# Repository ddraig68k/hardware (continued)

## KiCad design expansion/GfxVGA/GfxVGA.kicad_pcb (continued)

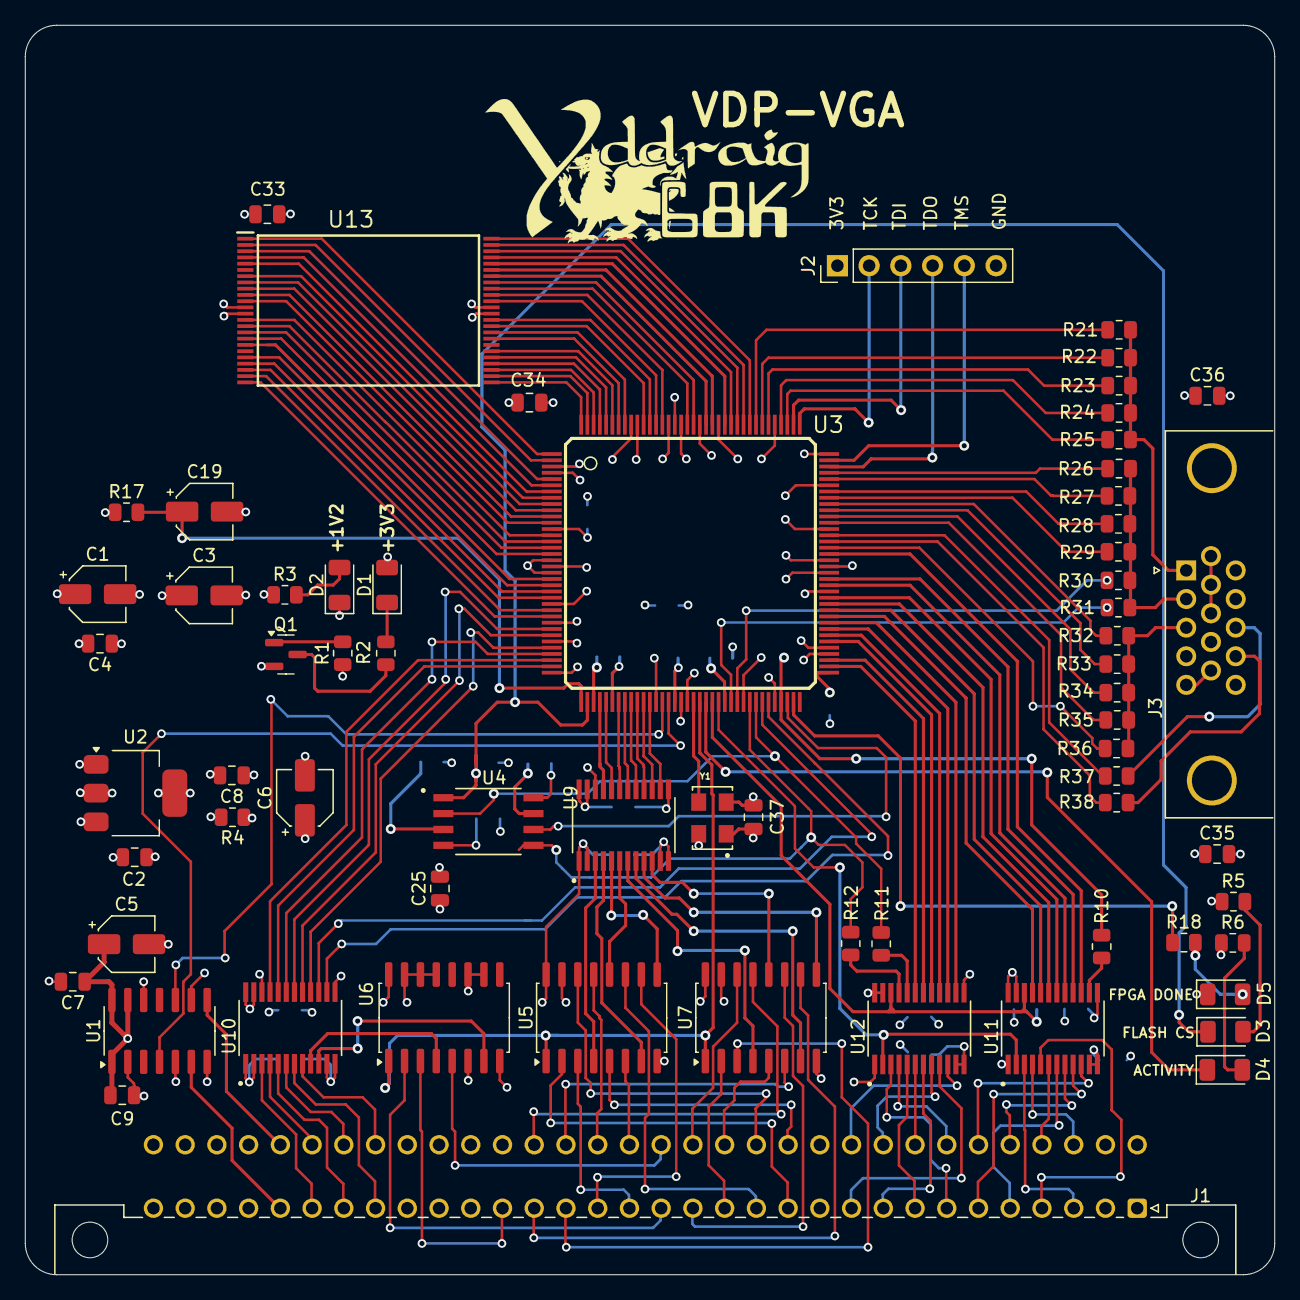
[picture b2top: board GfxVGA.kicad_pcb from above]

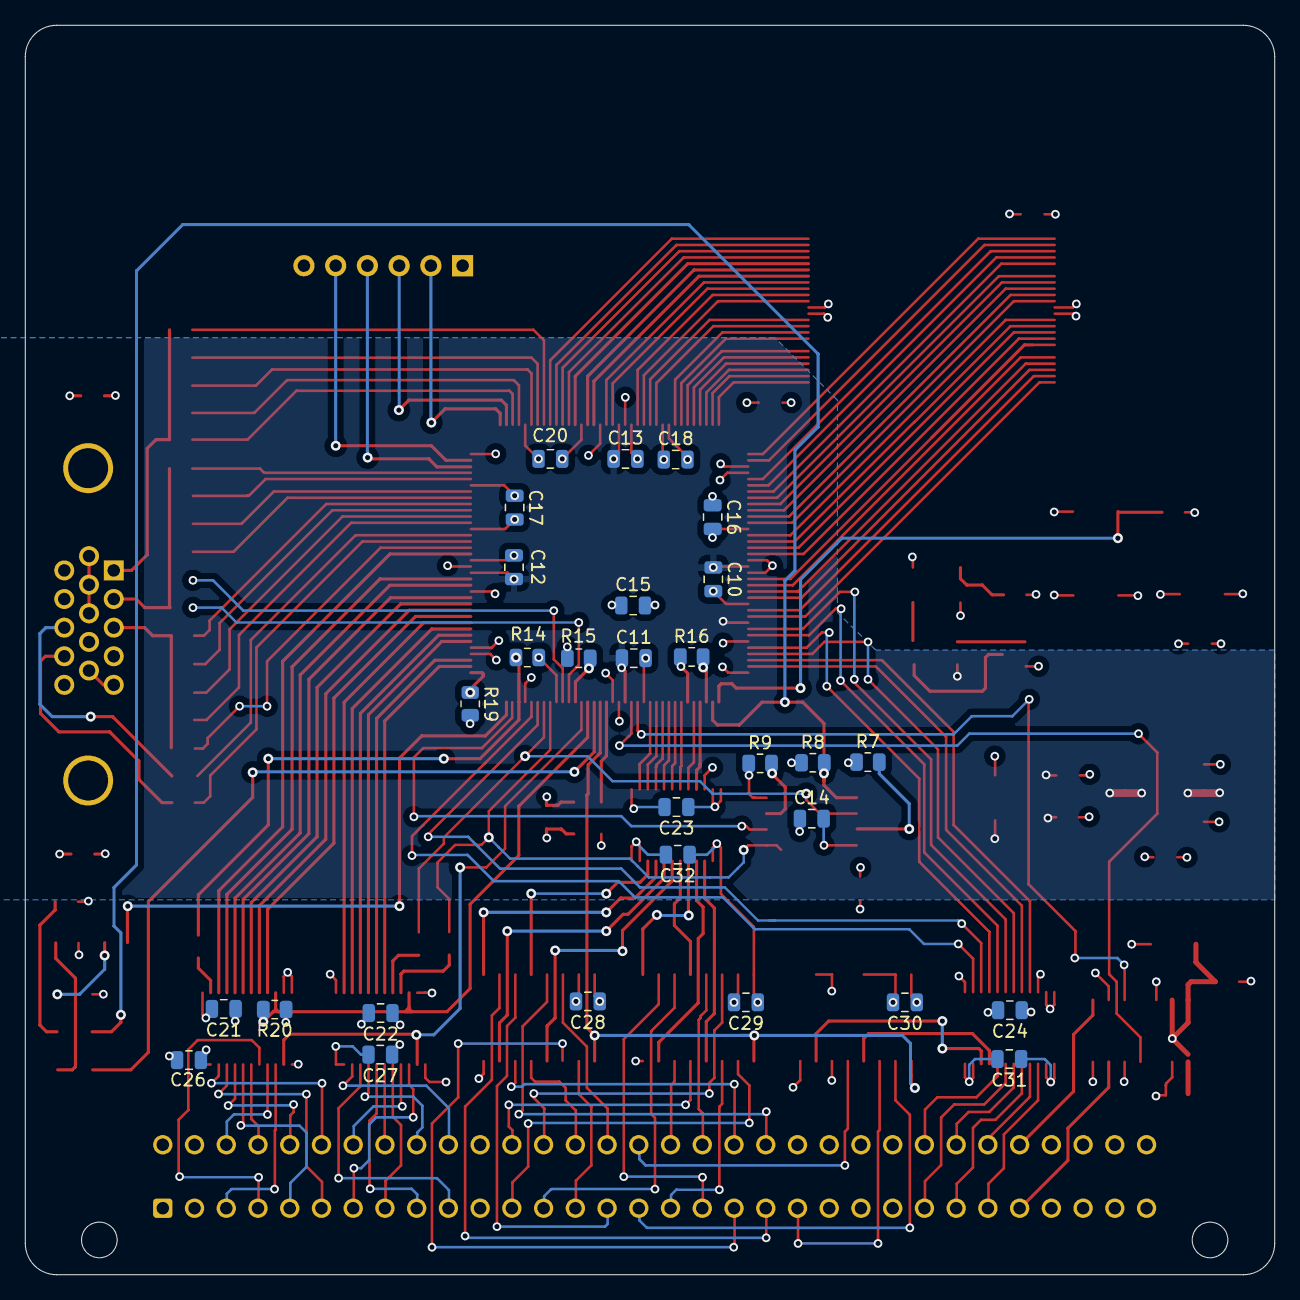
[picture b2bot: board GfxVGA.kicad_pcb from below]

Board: 4 copper layers, 100.0 x 100.0 mm, 97 parts (29 on the bottom side), 183 nets.

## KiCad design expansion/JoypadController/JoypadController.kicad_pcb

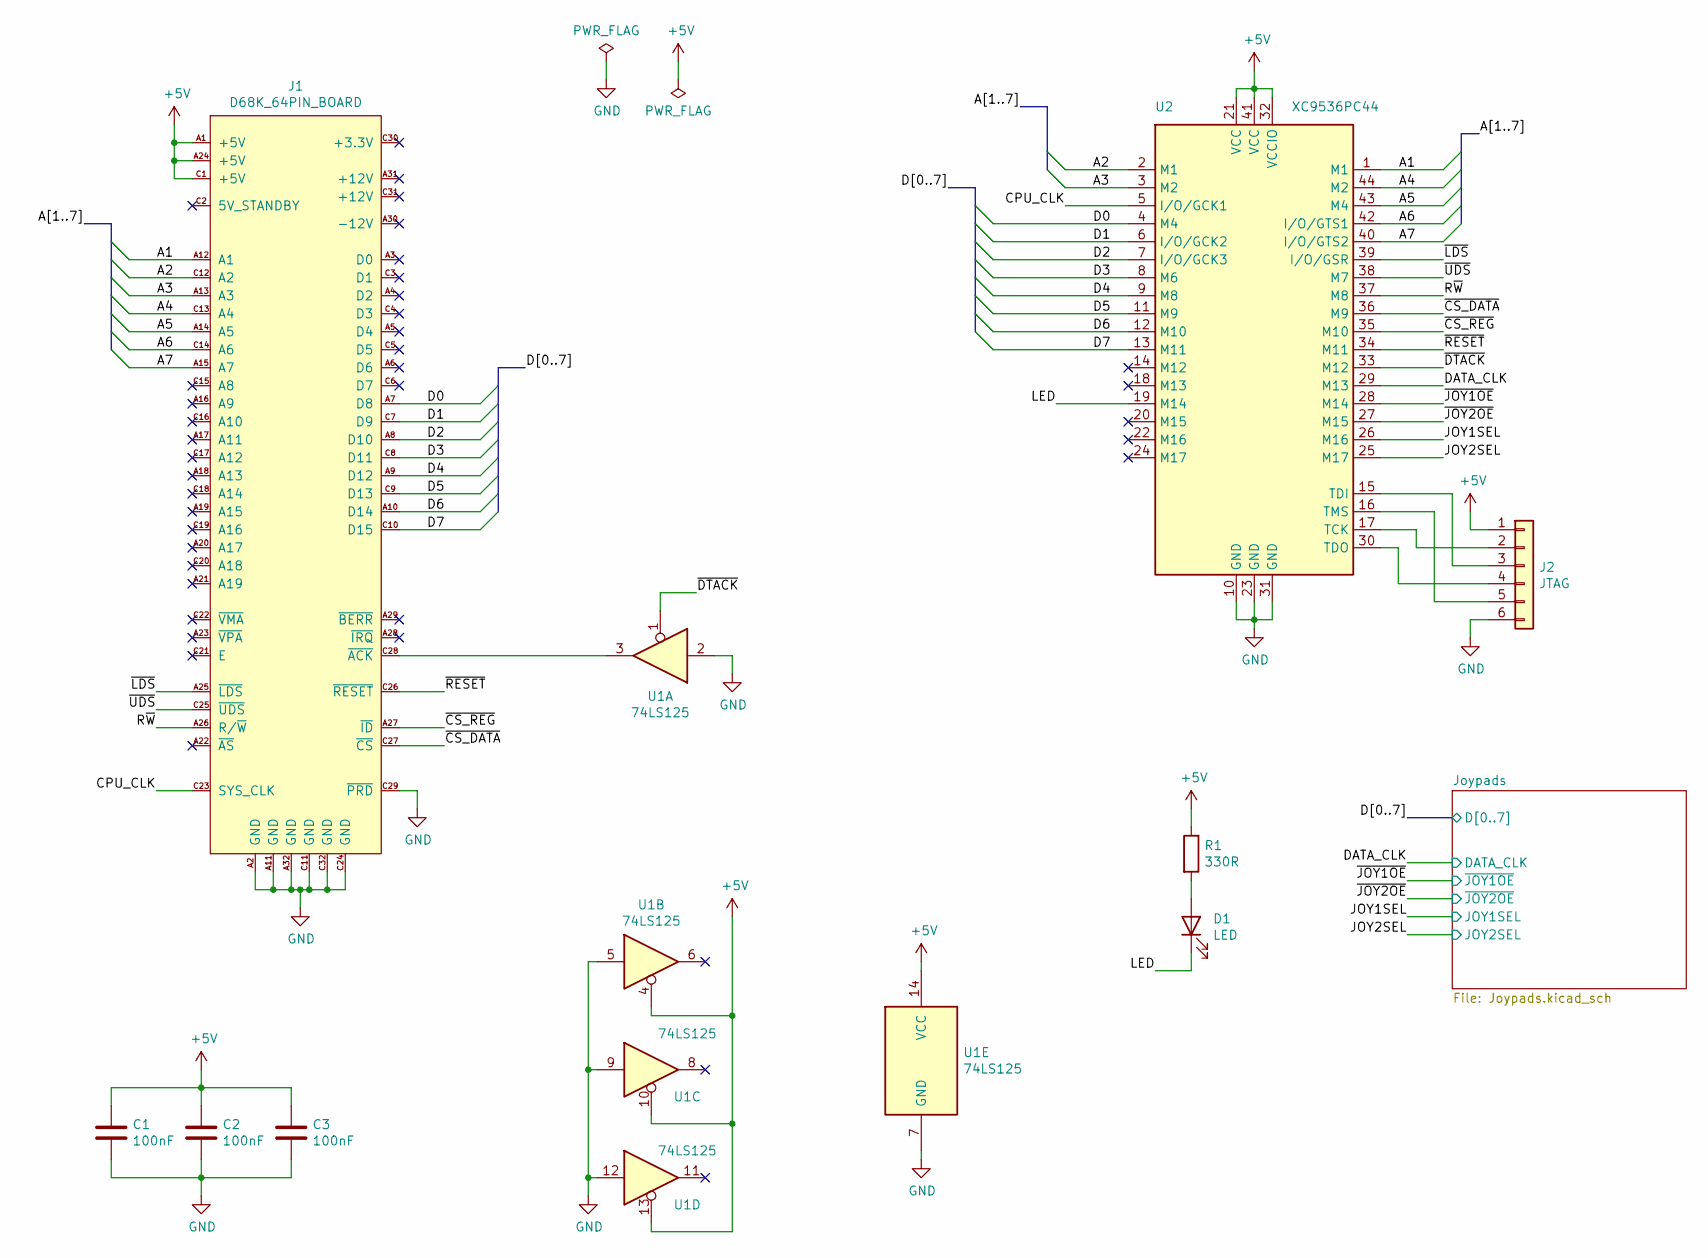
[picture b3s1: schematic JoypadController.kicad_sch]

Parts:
C1, C2, C3: 100nF; C_Disc_D5.0mm_W2.5mm_P2.50mm
D1: LED; LED_D5.0mm
J1: D68K_64PIN_BOARD; DIN41612_C_2x32_Male_Horizontal_THT
J2: JTAG; PinHeader_1x06_P2.54mm_Vertical
R1: 330R; R_Axial_DIN0207_L6.3mm_D2.5mm_P10.16mm_Horizontal
U1: 74LS125; DIP-14_W7.62mm_Socket
U2: XC9536PC44; PLCC-44

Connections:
+5V: C1.1, C2.1, C3.1, J1.A1 (+5V), J1.A24 (+5V), J1.C1 (+5V), J2.1, R1.1, U1.4, U1.10, U1.13, U1.14 (VCC), U2.21 (VCC), U2.32 (VCCIO), U2.41 (VCC); also elsewhere on the board
/A1: J1.A12 (A1), U2.1 (M1)
/A2: J1.C12 (A2), U2.2 (M1)
/A3: J1.A13 (A3), U2.3 (M2)
/A4: J1.C13 (A4), U2.44 (M2)
/A5: J1.A14 (A5), U2.43 (M4)
/A6: J1.C14 (A6), U2.42 (I/O/GTS1)
/A7: J1.A15 (A7), U2.40 (I/O/GTS2)
/CPU_CLK: J1.C23 (SYS_CLK), U2.5 (I/O/GCK1)
/D0: J1.A7 (D8), U2.4 (M4); also elsewhere on the board
/D1: J1.C7 (D9), U2.6 (I/O/GCK2); also elsewhere on the board
/D2: J1.A8 (D10), U2.7 (I/O/GCK3); also elsewhere on the board
/D3: J1.C8 (D11), U2.8 (M6); also elsewhere on the board
/D4: J1.A9 (D12), U2.9 (M8); also elsewhere on the board
/D5: J1.C9 (D13), U2.11 (M9); also elsewhere on the board
/D6: J1.A10 (D14), U2.12 (M10); also elsewhere on the board
/D7: J1.C10 (D15), U2.13 (M11); also elsewhere on the board
/DATA_CLK: U2.29 (M13); also elsewhere on the board
/JOY1SEL: U2.26 (M16); also elsewhere on the board
/JOY2SEL: U2.25 (M17); also elsewhere on the board
/LED: D1.1 (K), U2.19 (M14)
/R~W: J1.A26 (R/~W), U2.37 (M8)
/~CS_DATA: J1.C27 (~CS), U2.36 (M9)
/~CS_REG: J1.A27 (~ID), U2.35 (M10)
/~DTACK: U1.1, U2.33 (M12)
/~JOY1OE: U2.28 (M14); also elsewhere on the board
/~JOY2OE: U2.27 (M15); also elsewhere on the board
/~LDS: J1.A25 (~LDS), U2.39 (I/O/GSR)
/~RESET: J1.C26 (~RESET), U2.34 (M11)
/~UDS: J1.C25 (~UDS), U2.38 (M7)
GND: C1.2, C2.2, C3.2, J1.A2 (GND), J1.A11 (GND), J1.A32 (GND), J1.C11 (GND), J1.C24 (GND), J1.C29 (~PRD), J1.C32 (GND), J2.6, U1.2, U1.5, U1.7 (GND), U1.9, U1.12, U2.10 (GND), U2.23 (GND), U2.31 (GND); also elsewhere on the board
unnamed: D1.2 (A), R1.2
unnamed: J1.C28 (~ACK), U1.3
unnamed: J2.2, U2.17 (TCK)
unnamed: J2.3, U2.15 (TDI)
unnamed: J2.4, U2.30 (TDO)
unnamed: J2.5, U2.16 (TMS)

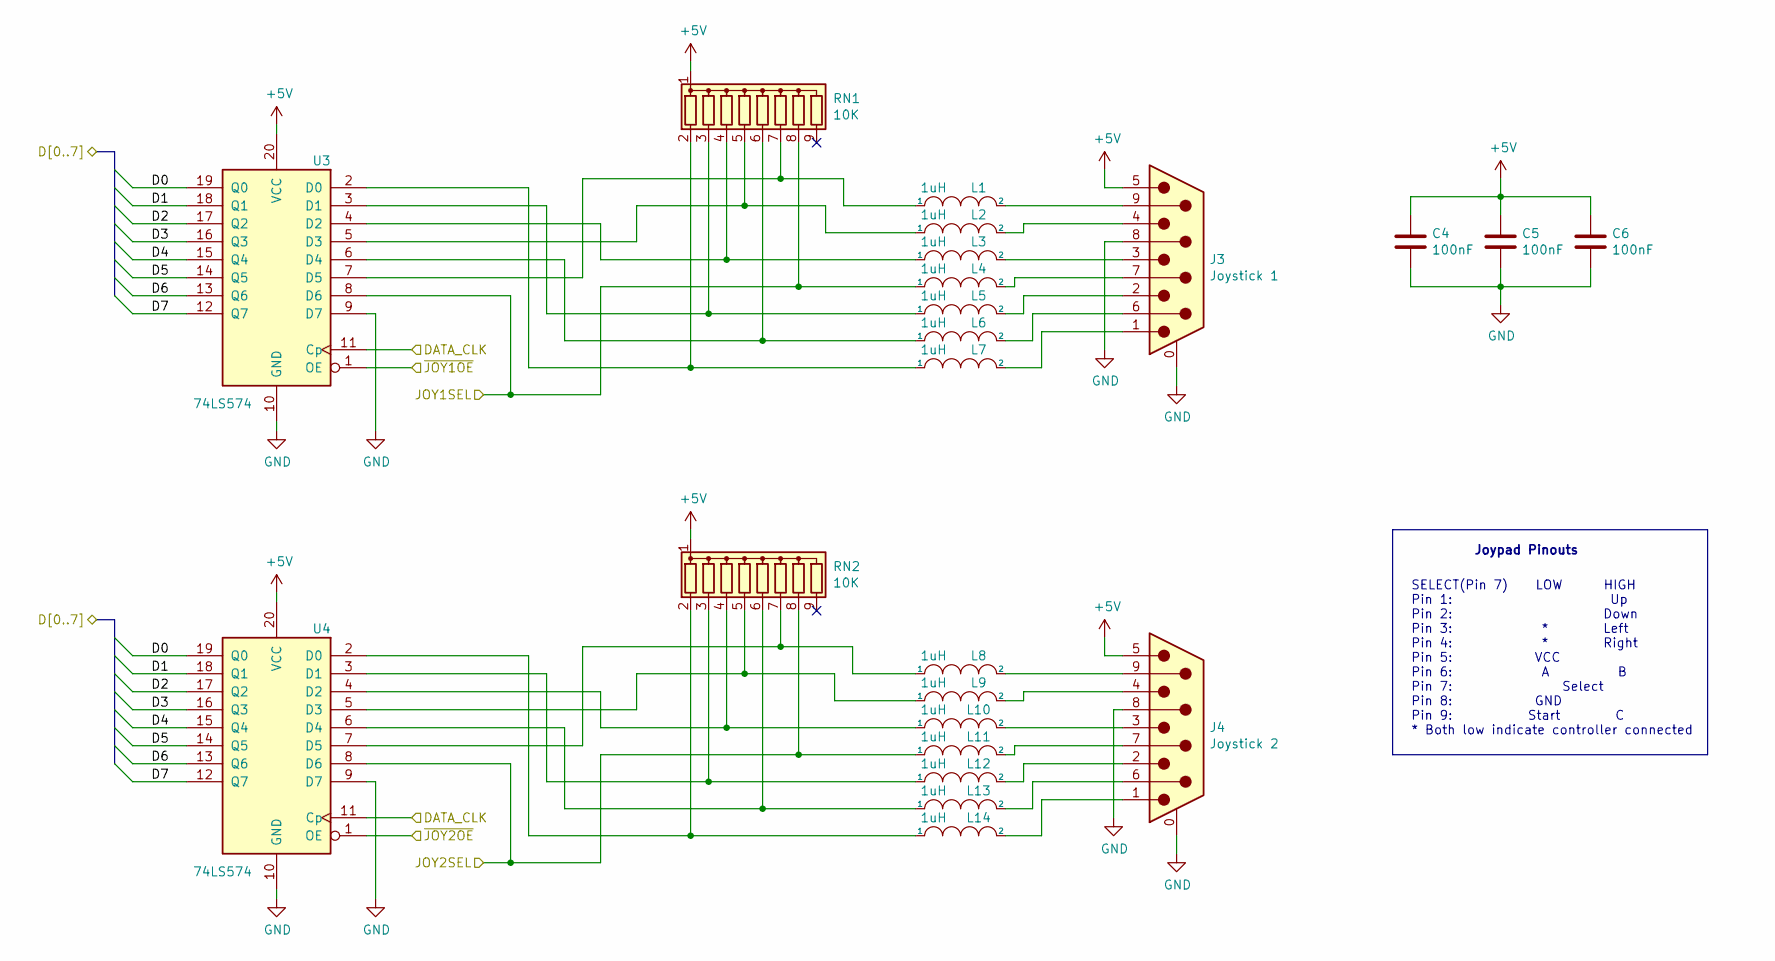
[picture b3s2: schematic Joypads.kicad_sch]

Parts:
C4, C5, C6: 100nF; C_Disc_D5.0mm_W2.5mm_P2.50mm
J3: Joystick 1; DSUB-9_Male_Horizontal_P2.77x2.84mm_EdgePinOffset4.94mm_Hou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
J4: Joystick 2; DSUB-9_Male_Horizontal_P2.77x2.84mm_EdgePinOffset4.94mm_Hou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
L1, L2, L3, L4, L5, L6, L7, L8, L9, L10, L11, L12, L13, L14: 1uH; L_Axial_L6.6mm_D2.7mm_P10.16mm_Horizontal_Vishay_IM-2
RN1, RN2: 10K; R_Array_SIP9
U3, U4: 74LS574; DIP-20_W7.62mm_Socket

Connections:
+5V: C4.1, C5.1, C6.1, J3.5, J4.5, RN1.1 (common), RN2.1 (common), U3.20 (VCC), U4.20 (VCC); also elsewhere on the board
/D0: U3.19 (Q0), U4.19 (Q0); also elsewhere on the board
/D1: U3.18 (Q1), U4.18 (Q1); also elsewhere on the board
/D2: U3.17 (Q2), U4.17 (Q2); also elsewhere on the board
/D3: U3.16 (Q3), U4.16 (Q3); also elsewhere on the board
/D4: U3.15 (Q4), U4.15 (Q4); also elsewhere on the board
/D5: U3.14 (Q5), U4.14 (Q5); also elsewhere on the board
/D6: U3.13 (Q6), U4.13 (Q6); also elsewhere on the board
/D7: U3.12 (Q7), U4.12 (Q7); also elsewhere on the board
/DATA_CLK: U3.11 (Cp), U4.11 (Cp); also elsewhere on the board
/JOY1SEL: L4.1, RN1.8 (R7), U3.8 (D6); also elsewhere on the board
/JOY2SEL: L11.1, RN2.8 (R7), U4.8 (D6); also elsewhere on the board
/~JOY1OE: U3.1 (OE); also elsewhere on the board
/~JOY2OE: U4.1 (OE); also elsewhere on the board
GND: C4.2, C5.2, C6.2, J3.0 (PAD), J3.8, J4.0 (PAD), J4.8, U3.9 (D7), U3.10 (GND), U4.9 (D7), U4.10 (GND); also elsewhere on the board
unnamed: J3.1, L7.2
unnamed: J3.2, L5.2
unnamed: J3.3, L3.2
unnamed: J3.4, L2.2
unnamed: J3.6, L6.2
unnamed: J3.7, L4.2
unnamed: J3.9, L1.2
unnamed: J4.1, L14.2
unnamed: J4.2, L12.2
unnamed: J4.3, L10.2
unnamed: J4.4, L9.2
unnamed: J4.6, L13.2
unnamed: J4.7, L11.2
unnamed: J4.9, L8.2
unnamed: L1.1, RN1.7 (R6), U3.7 (D5)
unnamed: L2.1, RN1.5 (R4), U3.5 (D3)
unnamed: L3.1, RN1.4 (R3), U3.4 (D2)
unnamed: L5.1, RN1.3 (R2), U3.3 (D1)
unnamed: L6.1, RN1.6 (R5), U3.6 (D4)
unnamed: L7.1, RN1.2 (R1), U3.2 (D0)
unnamed: L8.1, RN2.7 (R6), U4.7 (D5)
unnamed: L9.1, RN2.5 (R4), U4.5 (D3)
unnamed: L10.1, RN2.4 (R3), U4.4 (D2)
unnamed: L12.1, RN2.3 (R2), U4.3 (D1)
unnamed: L13.1, RN2.6 (R5), U4.6 (D4)
unnamed: L14.1, RN2.2 (R1), U4.2 (D0)

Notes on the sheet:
SELECT(Pin 7) LOW HIGH Pin 1: Up Pin 2: Down Pin 3: * Left Pin 4: * Right Pin 5: VCC Pin 6: A B Pin 7: Select Pin 8: GND Pin 9: Start C * Both low indicate controller connected
Joypad Pinouts

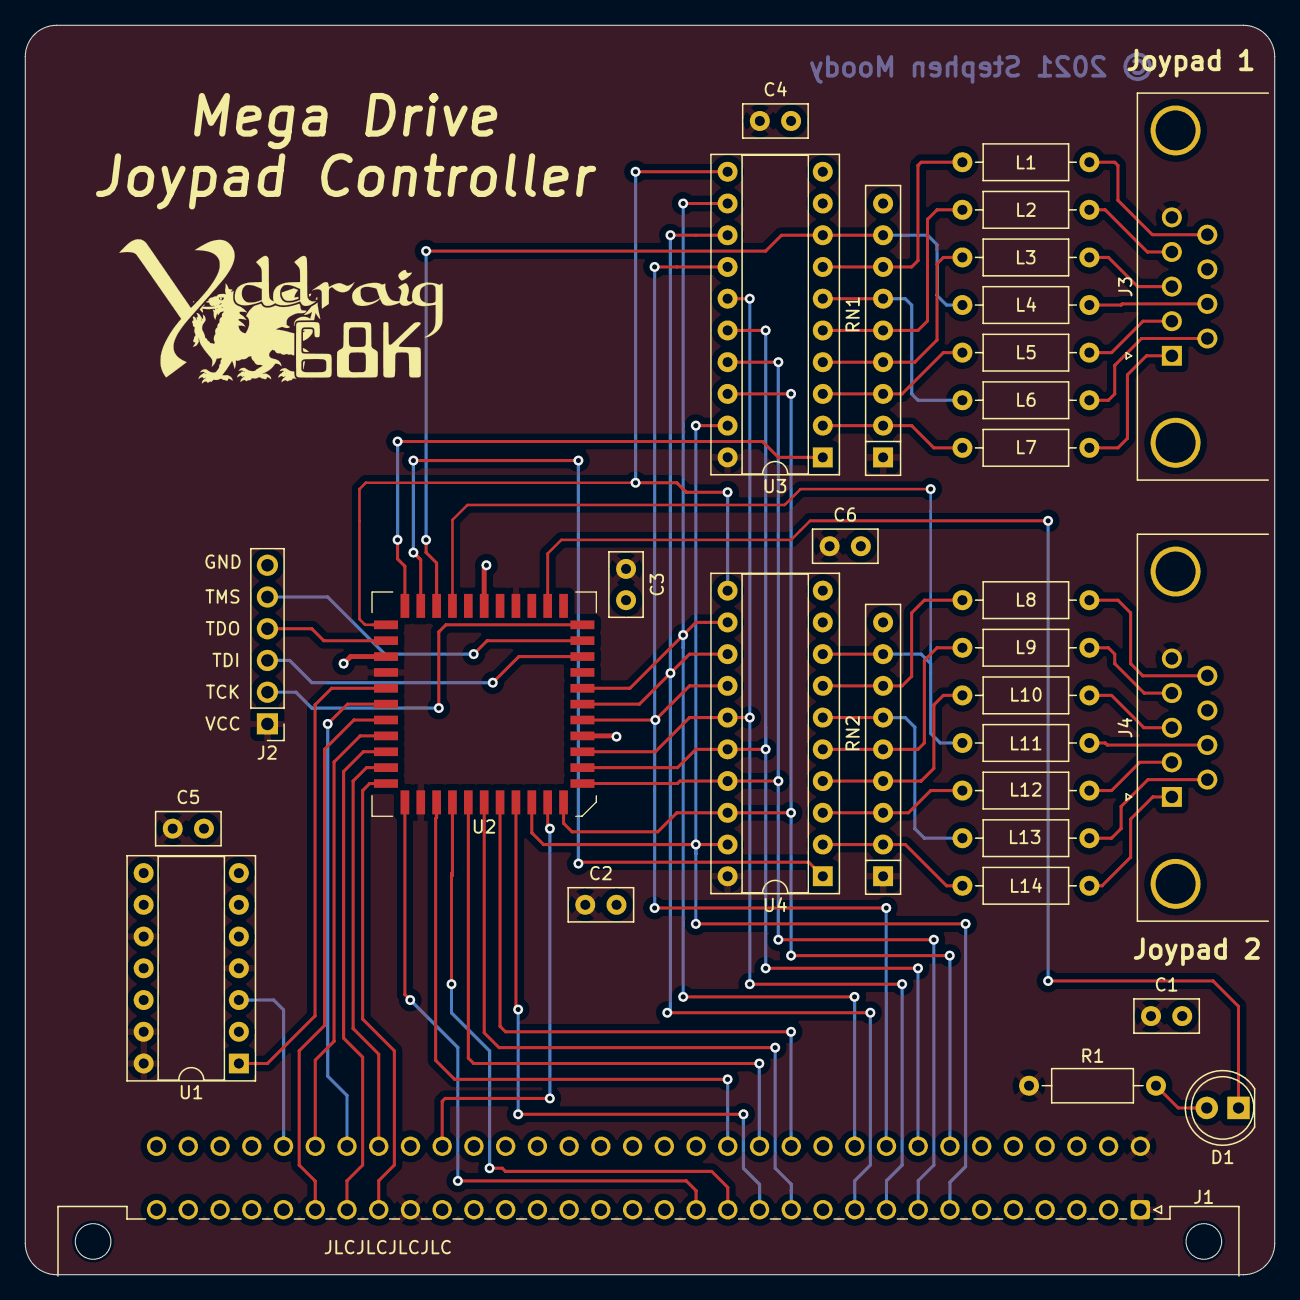
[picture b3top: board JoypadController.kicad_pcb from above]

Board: 2 copper layers, 100.0 x 100.0 mm, 32 parts (0 on the bottom side), 63 nets.

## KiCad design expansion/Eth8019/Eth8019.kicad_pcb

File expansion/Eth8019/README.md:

# RTL8019 Ethernet Card

The Realtek RTL8019AS is a fully integrated, single-chip [NE2000](https://en.wikipedia.org/wiki/NE2000)-compatible Ethernet controller with an 8/16-bit ISA-style bus interface and an integrated packet buffer, which makes it straightforward to attach to a simple non-DMA host bus like the 68000's.

A Xilinx XC9536PC44 CPLD provides the address decoding and glue logic between the expansion bus and the RTL8019AS, including the IOCS16B signalling used to negotiate 8/16-bit bus width with the host, as on ISA NE2000 cards.

The card has an RJ45 jack with integrated magnetics for the 10BASE-T connection, link/activity LEDs, and a JTAG header for programming the CPLD.

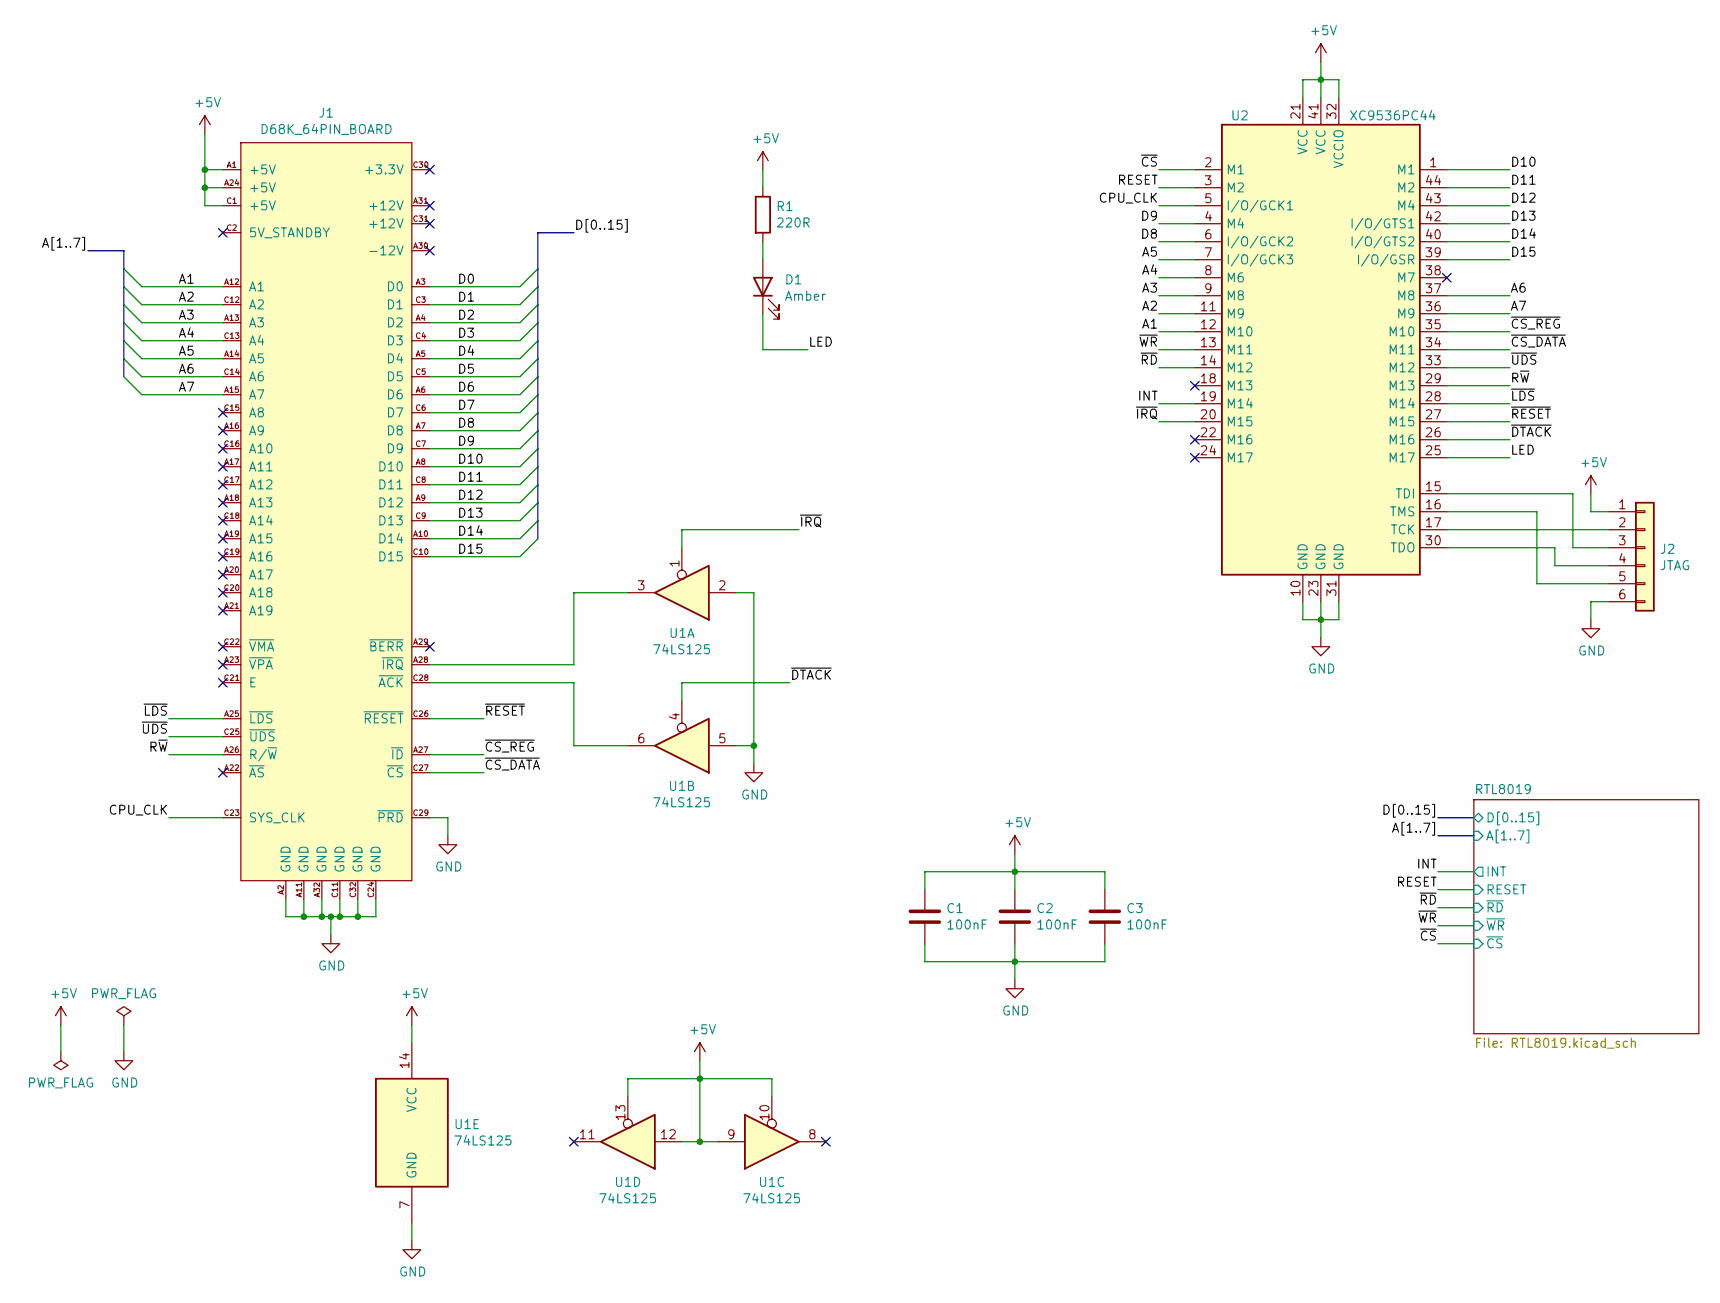
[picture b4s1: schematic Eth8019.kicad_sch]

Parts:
C1, C2, C3: 100nF; C_0805_2012Metric
D1: Amber; LED_1206_3216Metric
J1: D68K_64PIN_BOARD; DIN41612_C_2x32_Male_Horizontal_THT
J2: JTAG; PinHeader_1x06_P2.54mm_Vertical
R1: 220R; R_0805_2012Metric
U1: 74LS125; SO-14_5.3x10.2mm_P1.27mm
U2: XC9536PC44; PLCC-44

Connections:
+5V: C1.1, C2.1, C3.1, J1.A1 (+5V), J1.A24 (+5V), J1.C1 (+5V), J2.1, R1.1, U1.9, U1.10, U1.12, U1.13, U1.14 (VCC), U2.21 (VCC), U2.32 (VCCIO), U2.41 (VCC); also elsewhere on the board
/A1: J1.A12 (A1), U2.12 (M10); also elsewhere on the board
/A2: J1.C12 (A2), U2.11 (M9); also elsewhere on the board
/A3: J1.A13 (A3), U2.9 (M8); also elsewhere on the board
/A4: J1.C13 (A4), U2.8 (M6); also elsewhere on the board
/A5: J1.A14 (A5), U2.7 (I/O/GCK3); also elsewhere on the board
/A6: J1.C14 (A6), U2.37 (M8)
/A7: J1.A15 (A7), U2.36 (M9)
/CPU_CLK: J1.C23 (SYS_CLK), U2.5 (I/O/GCK1)
/D0: J1.A3 (D0); also elsewhere on the board
/D1: J1.C3 (D1); also elsewhere on the board
/D2: J1.A4 (D2); also elsewhere on the board
/D3: J1.C4 (D3); also elsewhere on the board
/D4: J1.A5 (D4); also elsewhere on the board
/D5: J1.C5 (D5); also elsewhere on the board
/D6: J1.A6 (D6); also elsewhere on the board
/D7: J1.C6 (D7); also elsewhere on the board
/D8: J1.A7 (D8), U2.6 (I/O/GCK2); also elsewhere on the board
/D9: J1.C7 (D9), U2.4 (M4); also elsewhere on the board
/D10: J1.A8 (D10), U2.1 (M1); also elsewhere on the board
/D11: J1.C8 (D11), U2.44 (M2); also elsewhere on the board
/D12: J1.A9 (D12), U2.43 (M4); also elsewhere on the board
/D13: J1.C9 (D13), U2.42 (I/O/GTS1); also elsewhere on the board
/D14: J1.A10 (D14), U2.40 (I/O/GTS2); also elsewhere on the board
/D15: J1.C10 (D15), U2.39 (I/O/GSR); also elsewhere on the board
/INT: U2.19 (M14); also elsewhere on the board
/LED: D1.1 (K), U2.25 (M17)
/RESET: U2.3 (M2); also elsewhere on the board
/R~W: J1.A26 (R/~W), U2.29 (M13)
/~CS_DATA: J1.C27 (~CS), U2.34 (M11)
/~CS_REG: J1.A27 (~ID), U2.35 (M10)
/~CS: U2.2 (M1); also elsewhere on the board
/~DTACK: U1.4, U2.26 (M16)
/~IRQ: U1.1, U2.20 (M15)
/~LDS: J1.A25 (~LDS), U2.28 (M14)
/~RD: U2.14 (M12); also elsewhere on the board
/~RESET: J1.C26 (~RESET), U2.27 (M15)
/~UDS: J1.C25 (~UDS), U2.33 (M12)
/~WR: U2.13 (M11); also elsewhere on the board
GND: C1.2, C2.2, C3.2, J1.A2 (GND), J1.A11 (GND), J1.A32 (GND), J1.C11 (GND), J1.C24 (GND), J1.C29 (~PRD), J1.C32 (GND), J2.6, U1.2, U1.5, U1.7 (GND), U2.10 (GND), U2.23 (GND), U2.31 (GND); also elsewhere on the board
unnamed: D1.2 (A), R1.2
unnamed: J1.A28 (~IRQ), U1.3
unnamed: J1.C28 (~ACK), U1.6
unnamed: J2.2, U2.17 (TCK)
unnamed: J2.3, U2.15 (TDI)
unnamed: J2.4, U2.30 (TDO)
unnamed: J2.5, U2.16 (TMS)

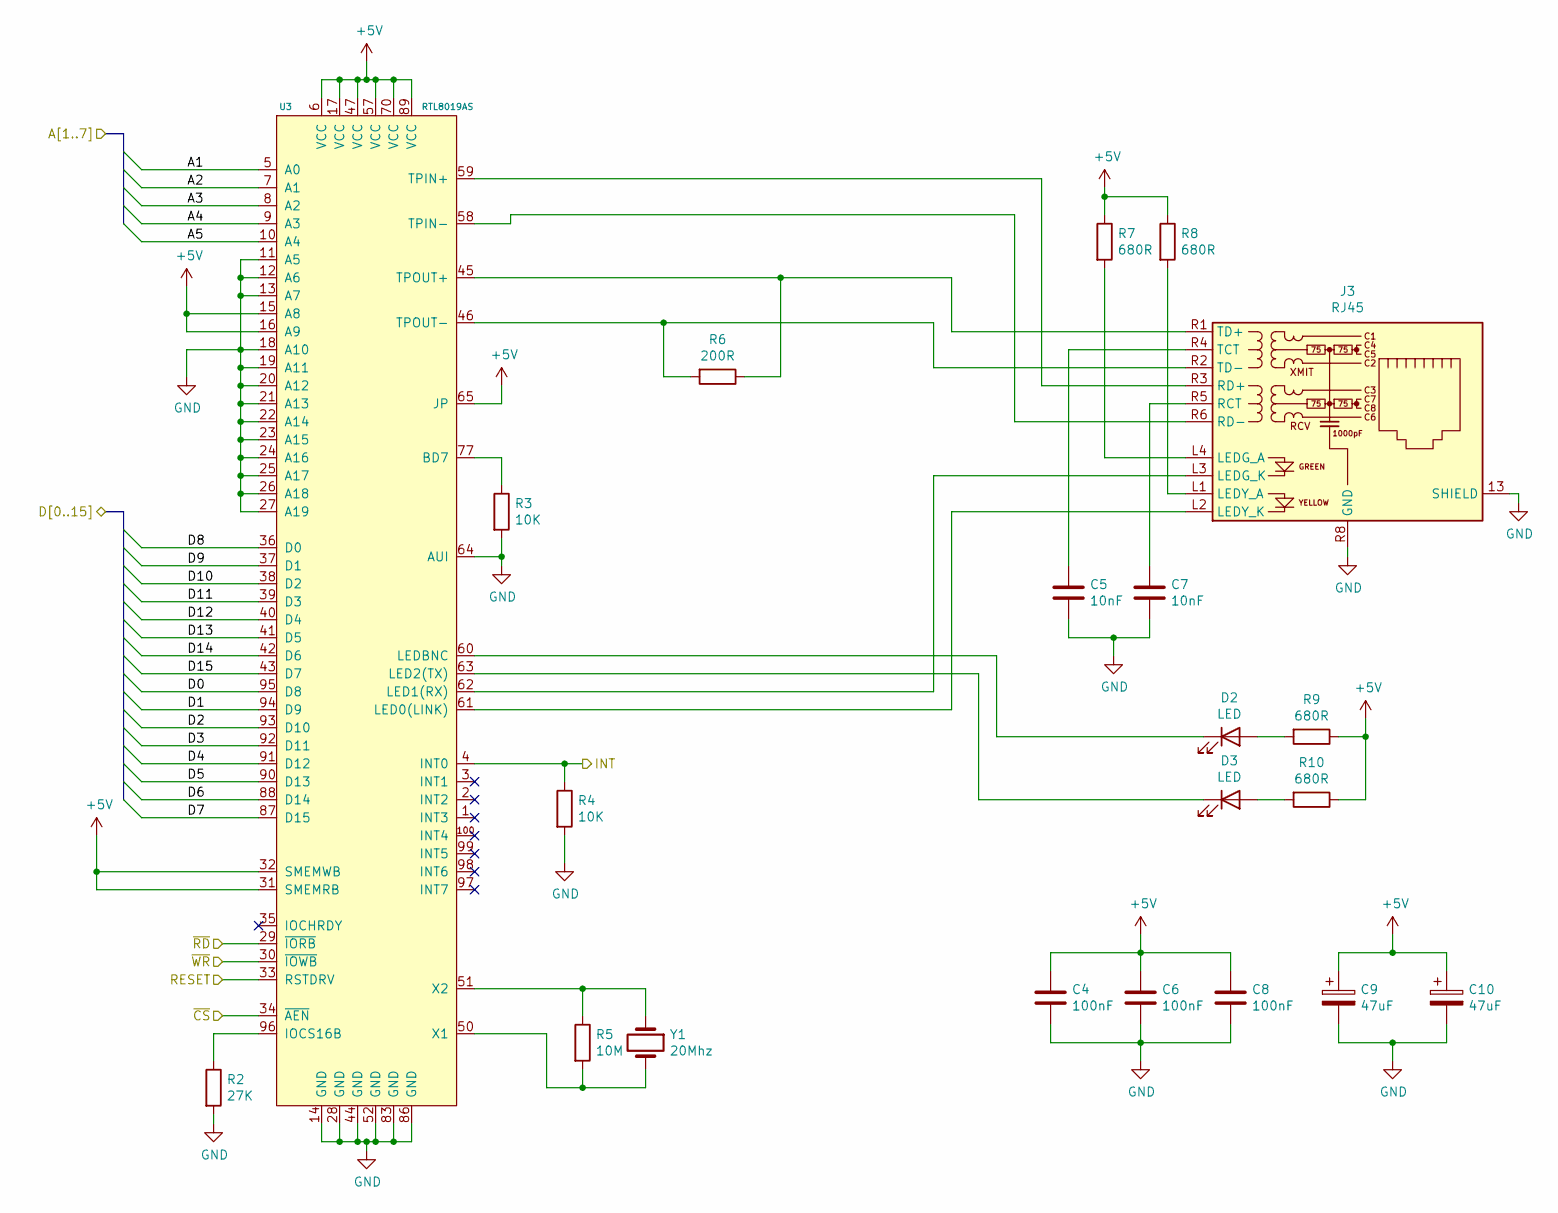
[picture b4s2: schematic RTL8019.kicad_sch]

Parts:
C4, C6, C8: 100nF; C_0805_2012Metric
C5, C7: 10nF; C_0805_2012Metric
C9, C10: 47uF; CP_Elec_4x5.7
D2, D3: LED; LED_1206_3216Metric
J3: RJ45; RJ45_Amphenol_RJMG1BD3B8K1ANR
R2: 27K; R_0805_2012Metric
R3, R4: 10K; R_0805_2012Metric
R5: 10M; R_0805_2012Metric
R6: 200R; R_0805_2012Metric
R7, R8, R9, R10: 680R; R_0805_2012Metric
U3: RTL8019AS
Y1: 20Mhz; Crystal_SMD_HC49-SD

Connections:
+5V: C4.1, C6.1, C8.1, C9.1, C10.1, R7.1, R8.1, R9.1, R10.1, U3.6 (VCC), U3.15 (A8), U3.16 (A9), U3.17 (VCC), U3.31 (SMEMRB), U3.32 (SMEMWB), U3.47 (VCC), U3.57 (VCC), U3.65 (JP), U3.70 (VCC), U3.89 (VCC); also elsewhere on the board
/A1: U3.5 (A0); also elsewhere on the board
/A2: U3.7 (A1); also elsewhere on the board
/A3: U3.8 (A2); also elsewhere on the board
/A4: U3.9 (A3); also elsewhere on the board
/A5: U3.10 (A4); also elsewhere on the board
/D0: U3.95 (D8); also elsewhere on the board
/D1: U3.94 (D9); also elsewhere on the board
/D2: U3.93 (D10); also elsewhere on the board
/D3: U3.92 (D11); also elsewhere on the board
/D4: U3.91 (D12); also elsewhere on the board
/D5: U3.90 (D13); also elsewhere on the board
/D6: U3.88 (D14); also elsewhere on the board
/D7: U3.87 (D15); also elsewhere on the board
/D8: U3.36 (D0); also elsewhere on the board
/D9: U3.37 (D1); also elsewhere on the board
/D10: U3.38 (D2); also elsewhere on the board
/D11: U3.39 (D3); also elsewhere on the board
/D12: U3.40 (D4); also elsewhere on the board
/D13: U3.41 (D5); also elsewhere on the board
/D14: U3.42 (D6); also elsewhere on the board
/D15: U3.43 (D7); also elsewhere on the board
/INT: R4.1, U3.4 (INT0); also elsewhere on the board
/RESET: U3.33 (RSTDRV); also elsewhere on the board
/~CS: U3.34 (~AEN); also elsewhere on the board
/~RD: U3.29 (~IORB); also elsewhere on the board
/~WR: U3.30 (~IOWB); also elsewhere on the board
GND: C4.2, C5.2, C6.2, C7.2, C8.2, C9.2, C10.2, J3.13 (SHIELD), J3.R8 (GND), R2.2, R3.2, R4.2, U3.11 (A5), U3.12 (A6), U3.13 (A7), U3.14 (GND), U3.18 (A10), U3.19 (A11), U3.20 (A12), U3.21 (A13), U3.22 (A14), U3.23 (A15), U3.24 (A16), U3.25 (A17), U3.26 (A18), U3.27 (A19), U3.28 (GND), U3.44 (GND), U3.52 (GND), U3.64 (AUI), U3.83 (GND), U3.86 (GND); also elsewhere on the board
unnamed: C5.1, J3.R4 (TCT)
unnamed: C7.1, J3.R5 (RCT)
unnamed: D2.1 (K), U3.60 (LEDBNC)
unnamed: D2.2 (A), R9.2
unnamed: D3.1 (K), U3.63 (LED2(TX))
unnamed: D3.2 (A), R10.2
unnamed: J3.L1 (LEDY_A), R8.2
unnamed: J3.L2 (LEDY_K), U3.61 (LED0(LINK))
unnamed: J3.L3 (LEDG_K), U3.62 (LED1(RX))
unnamed: J3.L4 (LEDG_A), R7.2
unnamed: J3.R1 (TD+), R6.1, U3.45 (TPOUT+)
unnamed: J3.R2 (TD-), R6.2, U3.46 (TPOUT-)
unnamed: J3.R3 (RD+), U3.59 (TPIN+)
unnamed: J3.R6 (RD-), U3.58 (TPIN-)
unnamed: R2.1, U3.96 (IOCS16B)
unnamed: R3.1, U3.77 (BD7)
unnamed: R5.1, U3.51 (X2), Y1.1
unnamed: R5.2, U3.50 (X1), Y1.2

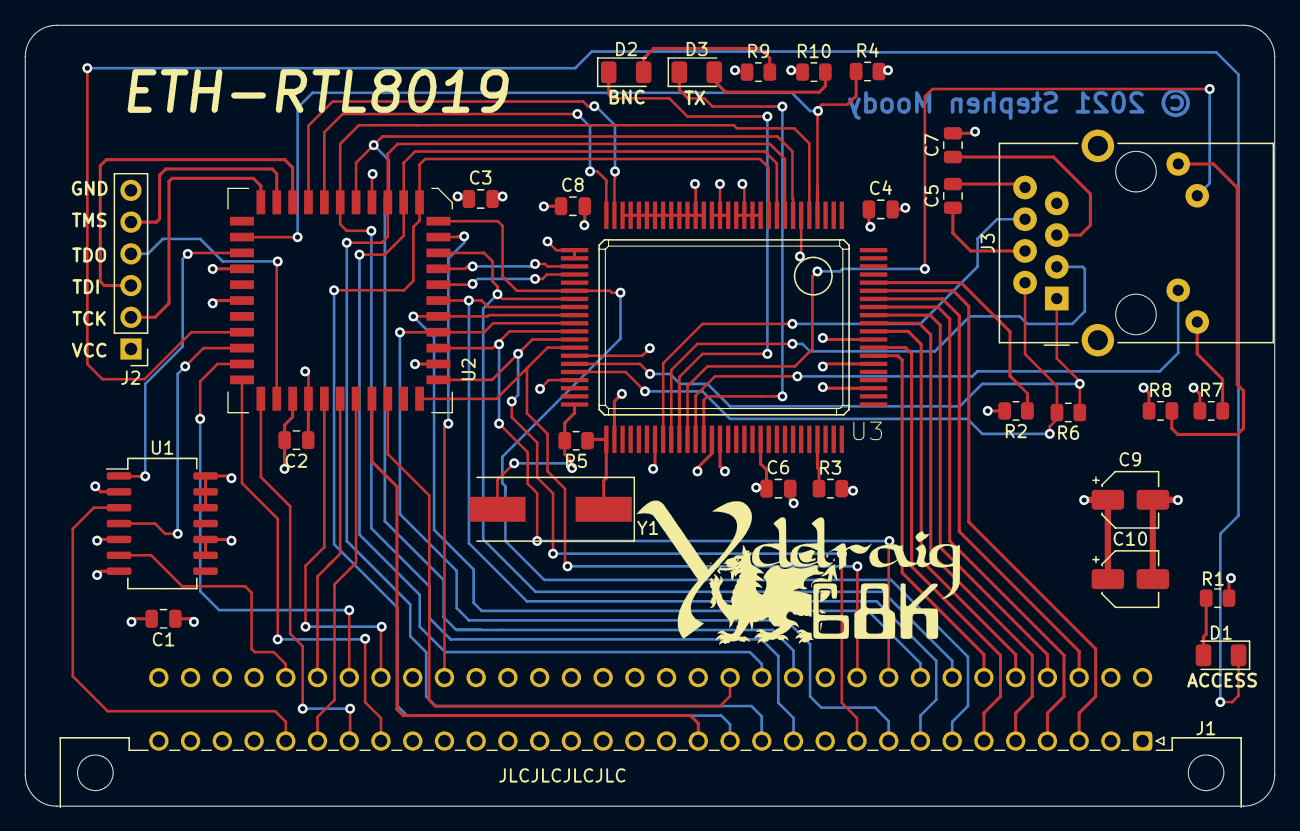
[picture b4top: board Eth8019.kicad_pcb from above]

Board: 4 copper layers, 100.0 x 62.5 mm, 30 parts (0 on the bottom side), 65 nets.
